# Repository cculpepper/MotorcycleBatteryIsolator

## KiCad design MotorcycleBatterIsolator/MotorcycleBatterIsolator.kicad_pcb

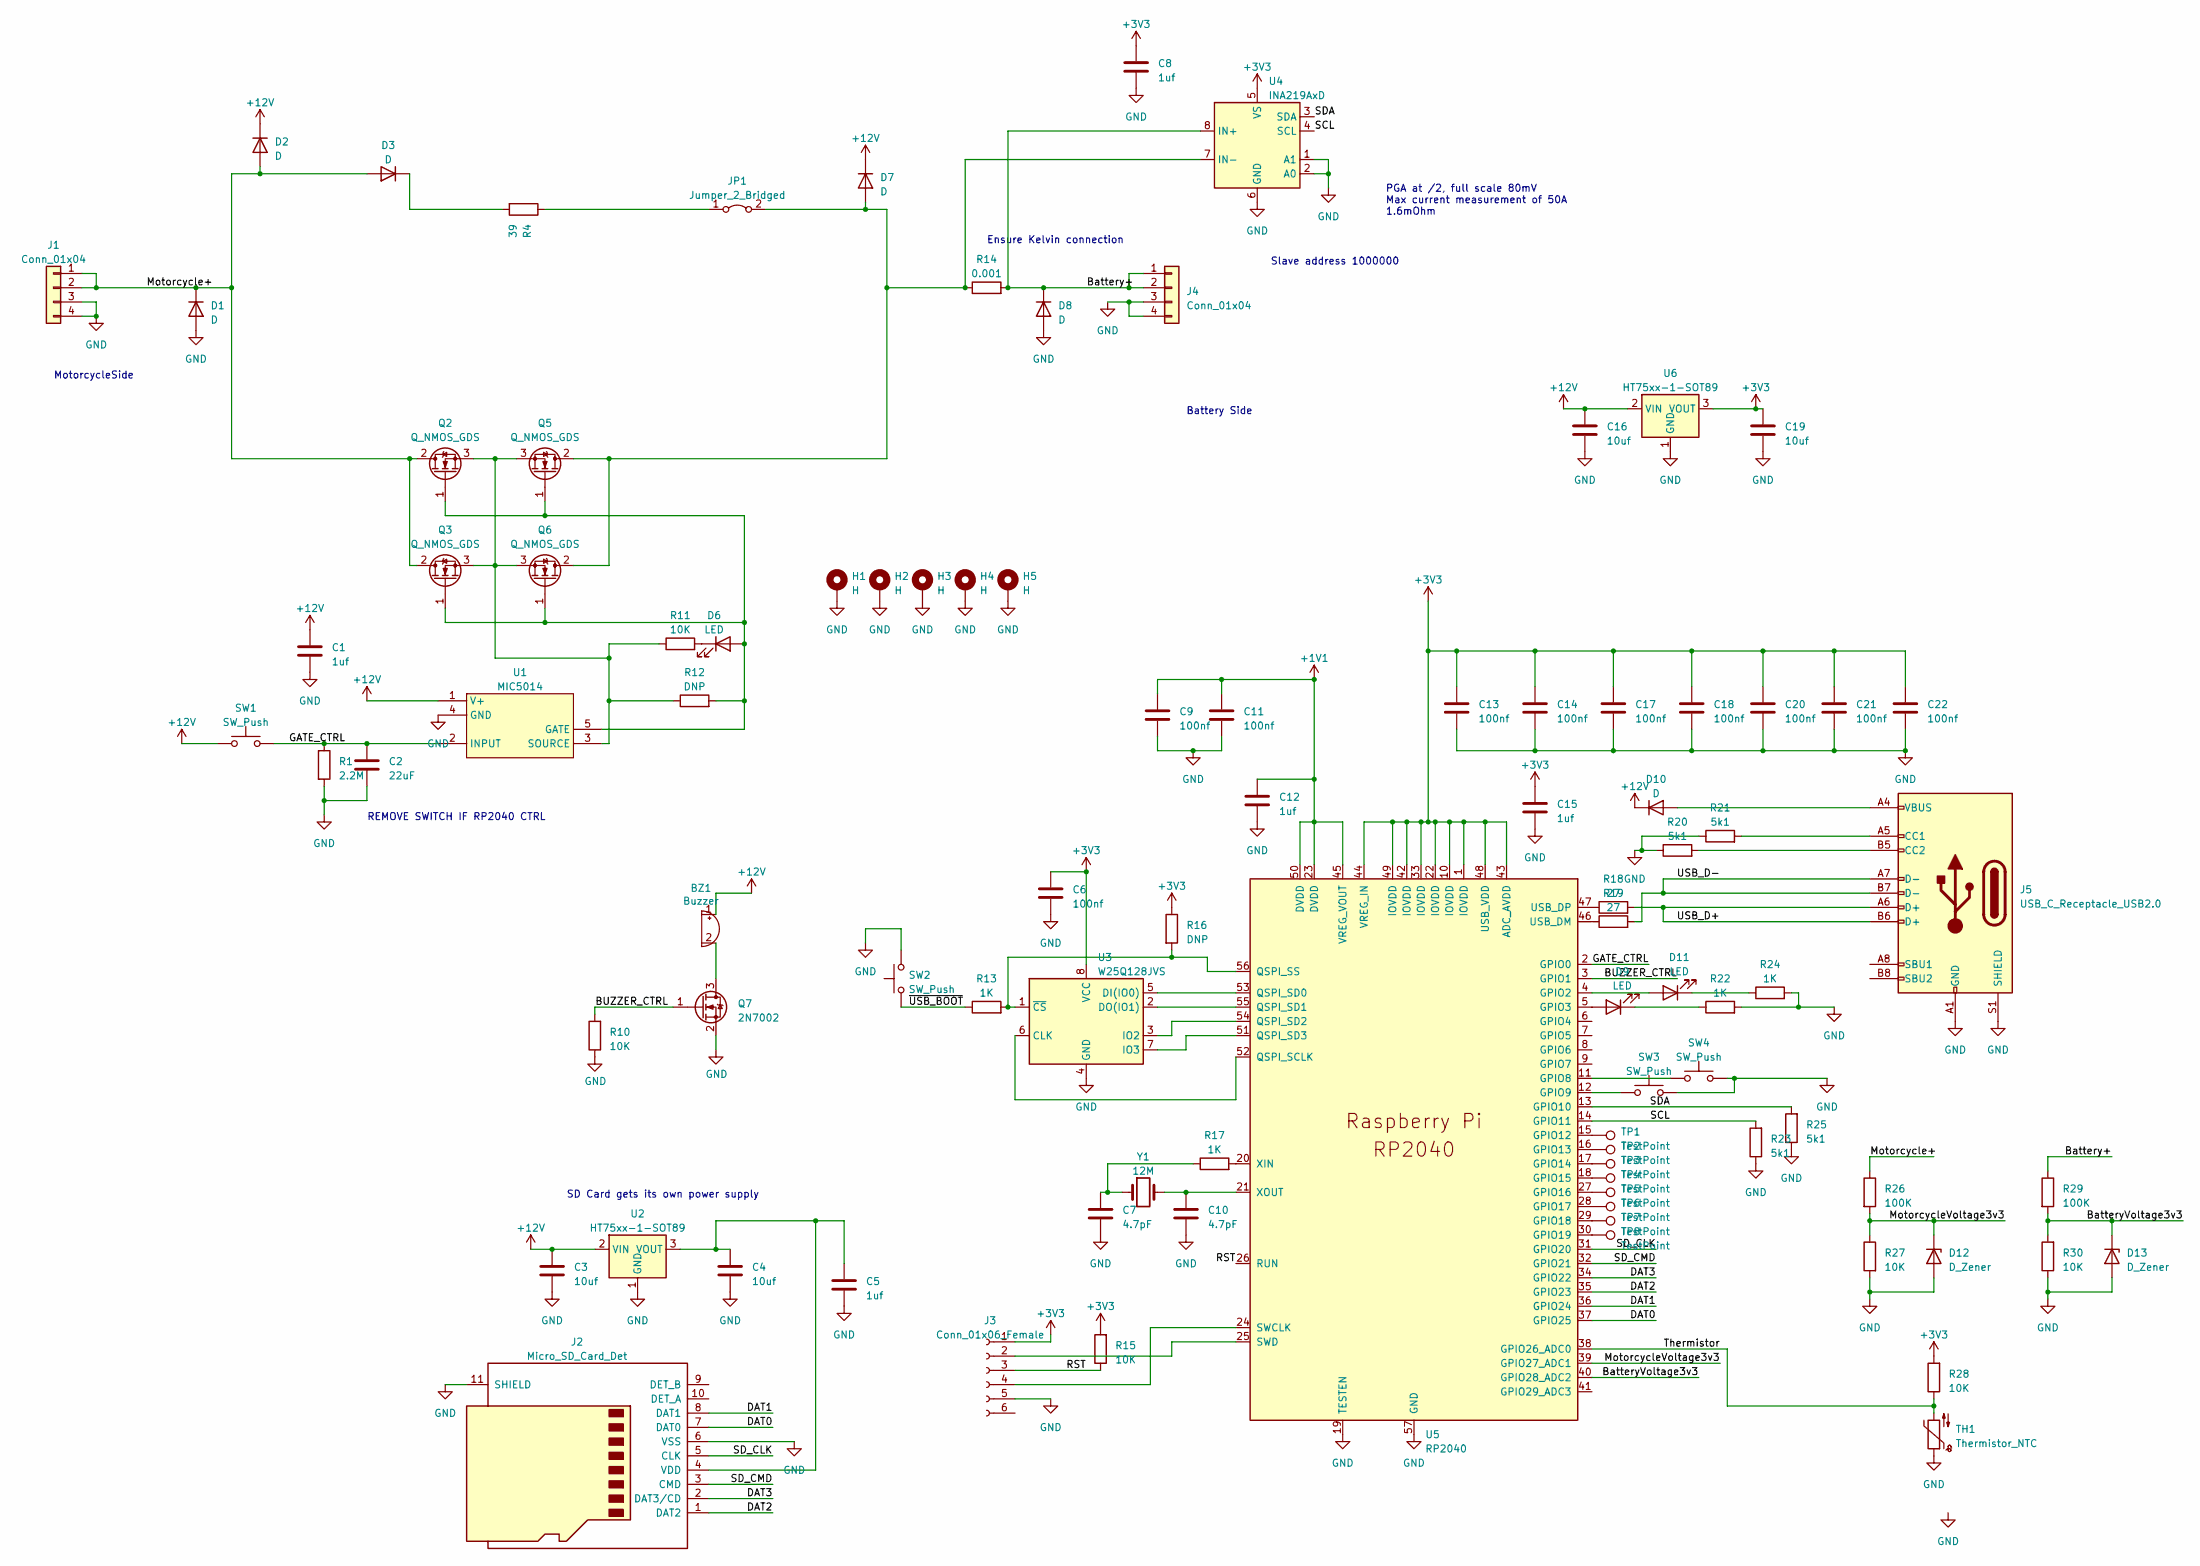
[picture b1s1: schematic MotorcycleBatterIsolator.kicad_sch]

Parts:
BZ1: Buzzer; MagneticBuzzer_ProSignal_ABT-410-RC; LCSCNotJLC C530340
C1, C5, C8, C12, C15: 1uf; C_0603_1608Metric; LCSC C15849
C2: 22uF; C_0805_2012Metric; LCSC C45783
C3, C4, C16, C19: 10uf; C_0603_1608Metric; LCSC C96446
C6, C9, C11, C13, C14, C17, C18, C20, C21, C22: 100nf; C_0603_1608Metric; LCSC C14663
C7, C10: 4.7pF; C_0603_1608Metric; LCSC C1669
D1, D2, D3, D7, D8, D10: D; D_SMA; LCSC C22452
D6, D9, D11: LED; LED_0603_1608Metric; LCSC C2286
D12, D13: D_Zener; D_MiniMELF; LCSC C8056
H1, H2, H3, H4, H5: H; MountingHole_3.2mm_M3_DIN965_Pad
J1, J4: Conn_01x04; APP_2x2
J2: Micro_SD_Card_Det; microSD_HC_Molex_104031-0811; LCSC C585350
J3: Conn_01x06_Female; Tag-Connect_TC2030-IDC-NL_2x03_P1.27mm_Vertical
J5: USB_C_Receptacle_USB2.0; USB_C_Receptacle_HRO_TYPE-C-31-M-12; LCSC C165948
JP1: Jumper_2_Bridged; SolderJumper-2_P1.3mm_Bridged2Bar_Pad1.0x1.5mm
Q2, Q3, Q5, Q6: Q_NMOS_GDS; TO-252-2; LCSC C127863
Q7: 2N7002; SOT-23; LCSC C8545
R1: 2.2M; R_0603_1608Metric; LCSC C22938
R4: 39; R2030; LCSC C175617
R10, R11, R15, R27, R28, R30: 10K; R_0603_1608Metric; LCSC C25804
R12, R16: DNP; R_0603_1608Metric
R13, R17, R22, R24: 1K; R_0603_1608Metric; LCSC C21190
R14: 0.001; R_2512_6332Metric; LCSC C312481
R18, R19: 27; R_0603_1608Metric; LCSC C25190
R20, R21, R23, R25: 5k1; R_0603_1608Metric; LCSC C23186
R26, R29: 100K; R_0603_1608Metric; LCSC C25803
SW1, SW2, SW3, SW4: SW_Push; SW_SPST_TL3342; LCSC C318884
TH1: Thermistor_NTC; PinHeader_1x02_P2.54mm_Horizontal
TP1, TP2, TP3, TP4, TP5, TP6, TP7, TP8: TestPoint; TestPoint_Pad_D1.0mm
U1: MIC5014; SOP-8_3.76x4.96mm_P1.27mm; LCSC C219121
U2, U6: HT75xx-1-SOT89; SOT-89-3; LCSC C14289
U3: W25Q128JVS; SOIC-8_5.23x5.23mm_P1.27mm; LCSC C97521
U4: INA219AxD; SOIC-8_3.9x4.9mm_P1.27mm; LCSC C138706
U5: RP2040; RP2040-QFN-56; LCSC C2040
Y1: 12M; Crystal_SMD_5032-2Pin_5.0x3.2mm; LCSC C90884

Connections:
+1V1: C9.1, C11.1, C12.1, U5.23 (DVDD), U5.45 (VREG_VOUT), U5.50 (DVDD)
+3V3: C6.1, C8.1, C13.1, C14.1, C15.1, C17.1, C18.1, C19.1, C20.1, C21.1, C22.1, J3.1, R15.2, R16.1, R28.2, U3.8 (VCC), U4.5 (VS), U5.1 (IOVDD), U5.10 (IOVDD), U5.22 (IOVDD), U5.33 (IOVDD), U5.42 (IOVDD), U5.43 (ADC_AVDD), U5.44 (VREG_IN), U5.48 (USB_VDD), U5.49 (IOVDD), U6.3 (VOUT)
+12V: BZ1.1 (-), C1.1, C3.1, C16.1, D2.1 (K), D7.1 (K), D10.1 (K), SW1.1, U1.1 (V+), U2.2 (VIN), U6.2 (VIN)
/BUZZER_CTRL: Q7.1 (G), R10.2, U5.3 (GPIO1)
/Battery+: D8.1 (K), J4.1, J4.2, R14.2, R29.1, U4.8 (IN+)
/BatteryVoltage3v3: D13.1 (K), R29.2, R30.2, U5.40 (GPIO28_ADC2)
/DAT0: J2.7 (DAT0), U5.37 (GPIO25)
/DAT1: J2.8 (DAT1), U5.36 (GPIO24)
/DAT2: J2.1 (DAT2), U5.35 (GPIO23)
/DAT3: J2.2 (DAT3/CD), U5.34 (GPIO22)
/GATE_CTRL: C2.1, R1.1, SW1.2, U1.2 (INPUT), U5.2 (GPIO0)
/Motorcycle+: D1.1 (K), D2.2 (A), D3.2 (A), J1.1, J1.2, Q2.2 (D), Q3.2 (D), R26.1
/MotorcycleVoltage3v3: D12.1 (K), R26.2, R27.1, U5.39 (GPIO27_ADC1)
/RST: J3.3, R15.1, U5.26 (RUN)
/SCL: R23.2, U4.4 (SCL), U5.14 (GPIO11)
/SDA: R25.2, U4.3 (SDA), U5.13 (GPIO10)
/SD_CLK: J2.5 (CLK), U5.31 (GPIO20)
/SD_CMD: J2.3 (CMD), U5.32 (GPIO21)
/Thermistor: R28.1, TH1.2, U5.38 (GPIO26_ADC0)
/USB_D+: J5.A6 (D+), J5.B6 (D+), R18.2
/USB_D-: J5.A7 (D-), J5.B7 (D-), R19.2
/~USB_BOOT: R13.1, SW2.1
GND: C1.2, C2.2, C3.2, C4.2, C5.2, C6.2, C7.2, C8.2, C9.2, C10.2, C11.2, C12.2, C13.2, C14.2, C15.2, C16.2, C17.2, C18.2, C19.2, C20.2, C21.2, C22.2, D1.2 (A), D8.2 (A), D12.2 (A), D13.2 (A), H1.1, H2.1, H3.1, H4.1, H5.1, J1.3, J1.4, J2.6 (VSS), J2.11 (SHIELD), J3.5, J4.3, J4.4, J5.A1 (GND), J5.A12 (GND), J5.B1 (GND), J5.B12 (GND), J5.S1 (SHIELD), Q7.2 (S), R1.2, R10.1, R20.1, R21.1, R22.2, R23.1, R24.2, R25.1, R27.2, R30.1, SW2.2, SW3.2, SW4.2, TH1.1, U1.4 (GND), U2.1 (GND), U3.4 (GND), U4.1 (A1), U4.2 (A0), U4.6 (GND), U5.19 (TESTEN), U5.57 (GND), U6.1 (GND)
unnamed: BZ1.2 (+), Q7.3 (D)
unnamed: C7.1, R17.1, Y1.1
unnamed: D3.1 (K), R4.2
unnamed: D6.2 (A), Q2.1 (G), Q3.1 (G), Q5.1 (G), Q6.1 (G), R12.2, U1.5 (GATE)
unnamed: D6.1 (K), R11.2
unnamed: D7.2 (A), JP1.2 (B), Q5.2 (D), Q6.2 (D), R14.1, U4.7 (IN-)
unnamed: D9.2 (A), U5.5 (GPIO3)
unnamed: D9.1 (K), R22.1
unnamed: D10.2 (A), J5.A4 (VBUS), J5.A9 (VBUS), J5.B4 (VBUS), J5.B9 (VBUS)
unnamed: D11.2 (A), U5.4 (GPIO2)
unnamed: D11.1 (K), R24.1
unnamed: C4.1, C5.1, J2.4 (VDD), U2.3 (VOUT)
unnamed: J3.2, U5.25 (SWD)
unnamed: J3.4, U5.24 (SWCLK)
unnamed: J5.A5 (CC1), R21.2
unnamed: J5.B5 (CC2), R20.2
unnamed: JP1.1 (A), R4.1
unnamed: Q2.3 (S), Q3.3 (S), Q5.3 (S), Q6.3 (S), R11.1, R12.1, U1.3 (SOURCE)
unnamed: U3.6 (CLK), U5.52 (QSPI_SCLK)
unnamed: U3.5 (DI(IO0)), U5.53 (QSPI_SD0)
unnamed: U3.2 (DO(IO1)), U5.55 (QSPI_SD1)
unnamed: U3.3 (IO2), U5.54 (QSPI_SD2)
unnamed: U3.7 (IO3), U5.51 (QSPI_SD3)
unnamed: R13.2, R16.2, U3.1 (~CS), U5.56 (QSPI_SS)
unnamed: SW4.1, U5.11 (GPIO8)
unnamed: SW3.1, U5.12 (GPIO9)
unnamed: TP1.1, U5.15 (GPIO12)
unnamed: TP2.1, U5.16 (GPIO13)
unnamed: TP3.1, U5.17 (GPIO14)
unnamed: TP4.1, U5.18 (GPIO15)
unnamed: TP5.1, U5.27 (GPIO16)
unnamed: TP6.1, U5.28 (GPIO17)
unnamed: TP7.1, U5.29 (GPIO18)
unnamed: TP8.1, U5.30 (GPIO19)
unnamed: R19.1, U5.46 (USB_DM)
unnamed: R18.1, U5.47 (USB_DP)
unnamed: R17.2, U5.20 (XIN)
unnamed: C10.1, U5.21 (XOUT), Y1.2

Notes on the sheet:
PGA at /2, full scale 80mV Max current measurement of 50A 1.6mOhm
SD Card gets its own power supply
Slave address 1000000
MotorcycleSide
Ensure Kelvin connection
REMOVE SWITCH IF RP2040 CTRL
Battery Side

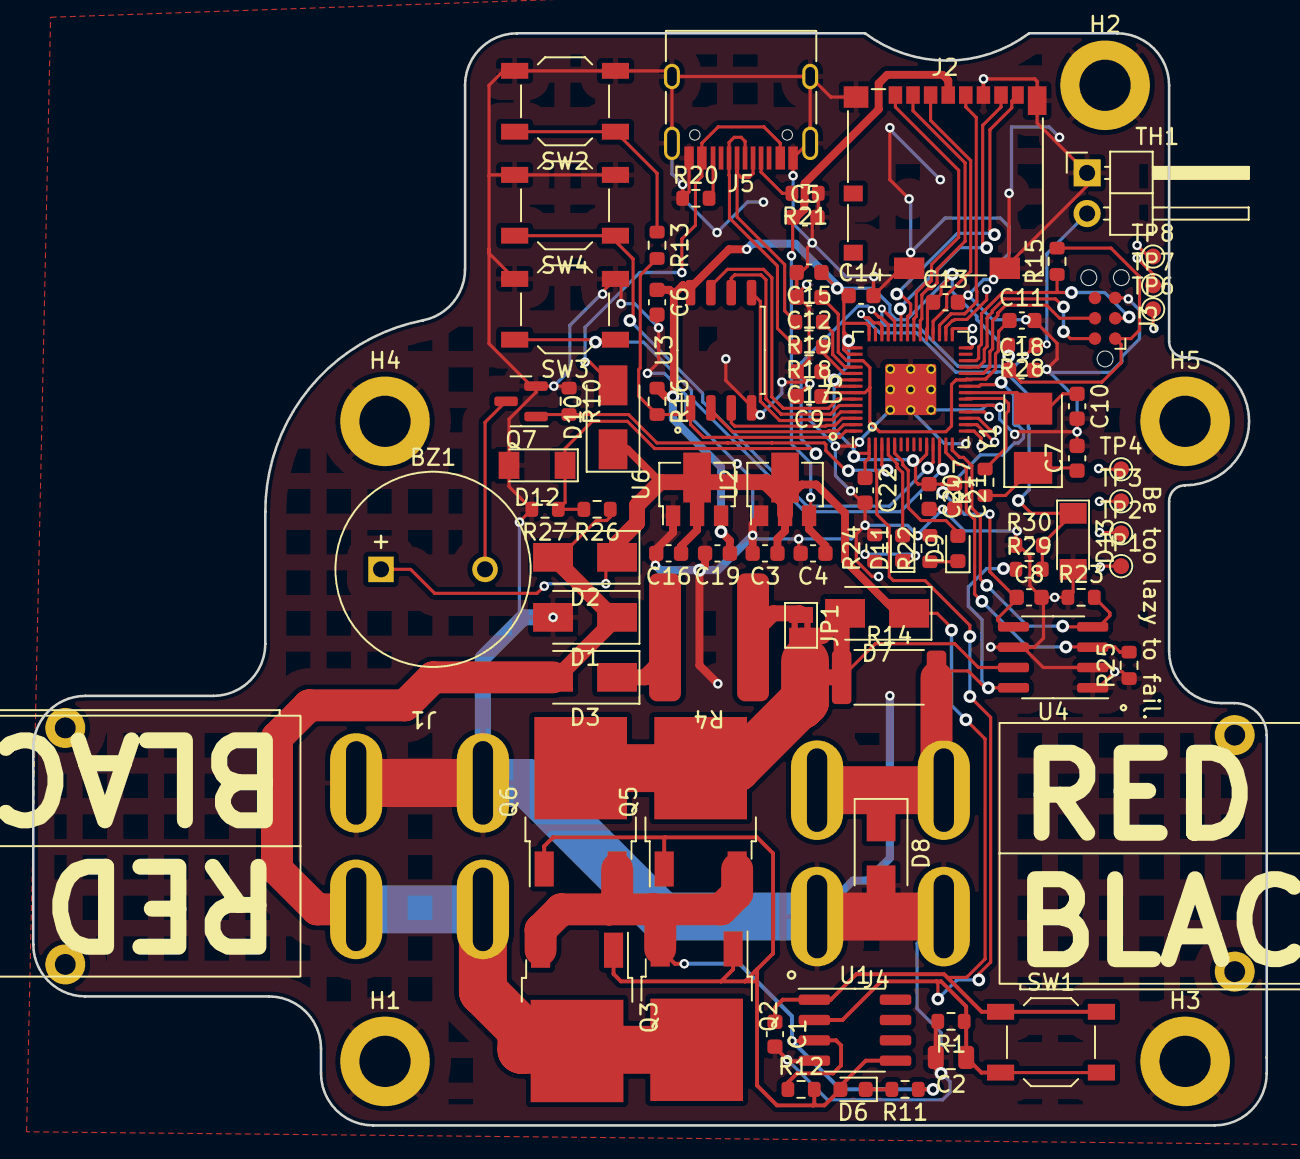
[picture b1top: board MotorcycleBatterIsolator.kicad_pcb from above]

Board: 4 copper layers, 77.1 x 68.2 mm, 92 parts (0 on the bottom side), 60 nets.

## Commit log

2022-02-13 INitial commit before I switch back to high side switching w/gate driver
2022-02-14 Finally onto the PCB. SHould just be a route job then sending it off
2022-03-02 This is the version that got sent off to fab
2022-03-10 Added issues tracker, also did some programming
2022-03-14 Started work on the firmware, removed backups
2022-03-15 The python logger works pretty well. Need to make it actually do the right thingsgs now!
